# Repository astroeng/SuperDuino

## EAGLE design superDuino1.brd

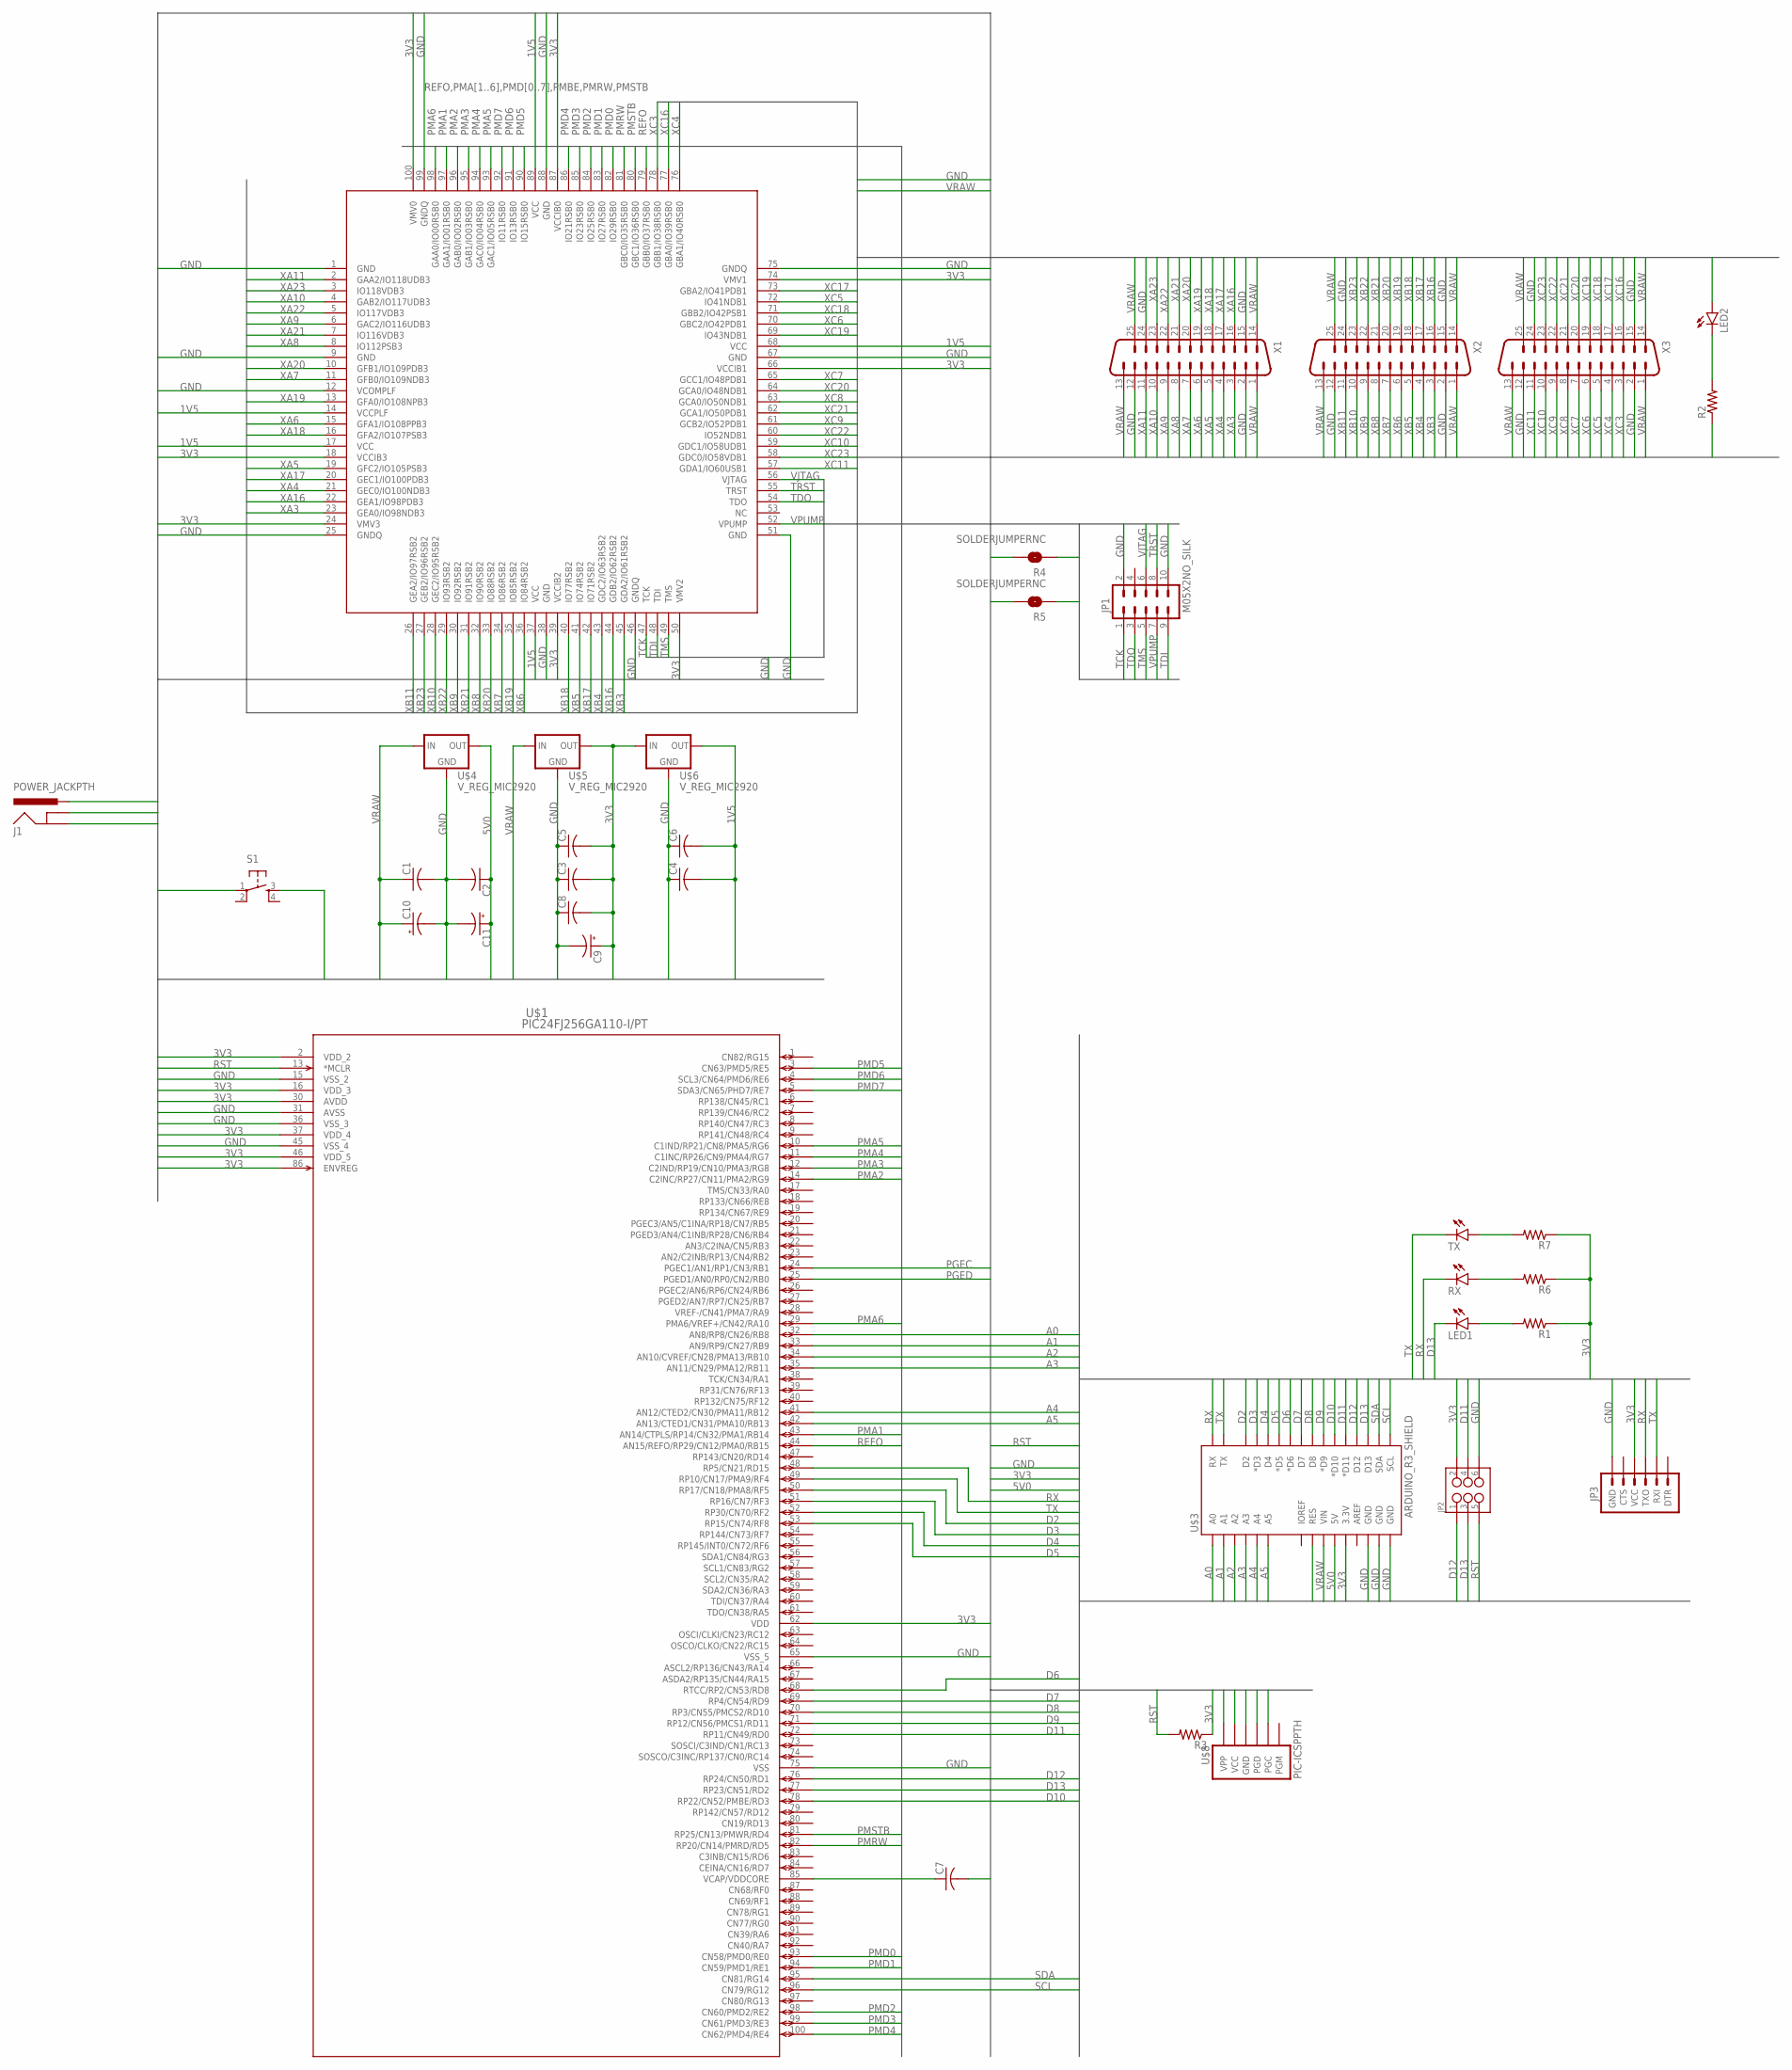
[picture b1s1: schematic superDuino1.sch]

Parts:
C1, C2, C3, C4, C5, C6, C8: C-USC0805; C0805
C7: C-US050-035X075; C050-035X075
C9, C10, C11: CPOL-USE2.5-6; E2,5-6
J1: POWER_JACKPTH; POWER_JACK_PTH
JP1: M05X2NO_SILK; 2X5_NOSILK
JP2: M03X22X3_SILK_SM; 2X3
JP3: ARDUINO_SERIAL_PROGRAMPTH; 1X06
LED1, LED2: LED1206; LED-1206
R1, R2, R3, R6, R7: R-US_R0805; R0805
R4, R5: SOLDERJUMPERNC; SJ_2S
RX: LED1206; LED-1206
S1: TAC_SWITCHPTH; TACTILE-PTH
TX: LED1206; LED-1206
U$1: PIC24FJ256GA110-I/PT; TQFP100_12X12MC
U$2: A3P250-VQ100; VQ100
U$3: ARDUINO_R3_SHIELD; UNO_R3_SHIELD
U$4, U$5, U$6: V_REG_MIC2920; SOT223
U$8: PIC-ICSPPTH; MOLEX-1X6
X1, X2, X3: DB25H; M25H

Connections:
1V5: C4.2, C6.2, U$2.14 (VCCPLF), U$2.17 (VCC), U$2.37 (VCC), U$2.68 (VCC), U$2.89 (VCC), U$6.3 (OUT)
3V3: C3.2, C5.2, C8.2, C9.+, JP2.2, JP3.VCC, R1.1, R3.1, R4.2, R5.2, R6.1, R7.1, U$1.2 (VDD_2), U$1.16 (VDD_3), U$1.30 (AVDD), U$1.37 (VDD_4), U$1.46 (VDD_5), U$1.62 (VDD), U$1.86 (ENVREG), U$2.18 (VCCIB3), U$2.24 (VMV3), U$2.39 (VCCIB2), U$2.50 (VMV2), U$2.66 (VCCIB1), U$2.74 (VMV1), U$2.87 (VCCIB0), U$2.100 (VMV0), U$3.3.3V, U$5.3 (OUT), U$6.1 (IN), U$8.5 (VCC)
5V0: C2.1, C11.+, U$3.5V, U$4.3 (OUT)
A0: U$1.32 (AN8/RP8/CN26/RB8), U$3.A0
A1: U$1.33 (AN9/RP9/CN27/RB9), U$3.A1
A2: U$1.34 (AN10/CVREF/CN28/PMA13/RB10), U$3.A2
A3: U$1.35 (AN11/CN29/PMA12/RB11), U$3.A3
A4: U$1.41 (AN12/CTED2/CN30/PMA11/RB12), U$3.A4
A5: U$1.42 (AN13/CTED1/CN31/PMA10/RB13), U$3.A5
D2: U$1.50 (RP17/CN18/PMA8/RF5), U$3.D2
D3: U$1.51 (RP16/CN7/RF3), U$3.D3 (*D3)
D4: U$1.52 (RP30/CN70/RF2), U$3.D4
D5: U$1.53 (RP15/CN74/RF8), U$3.D5 (*D5)
D6: U$1.68 (RTCC/RP2/CN53/RD8), U$3.D6 (*D6)
D7: U$1.69 (RP4/CN54/RD9), U$3.D7
D8: U$1.70 (RP3/CN55/PMCS2/RD10), U$3.D8
D9: U$1.71 (RP12/CN56/PMCS1/RD11), U$3.D9 (*D9)
D10: U$1.78 (RP22/CN52/PMBE/RD3), U$3.D10 (*D10)
D11: JP2.4, U$1.72 (RP11/CN49/RD0), U$3.D11 (*D11)
D12: JP2.1, U$1.76 (RP24/CN50/RD1), U$3.D12
D13: JP2.3, LED1.C, U$1.77 (RP23/CN51/RD2), U$3.D13
GND: C1.2, C2.2, C3.1, C4.1, C5.1, C6.1, C7.2, C8.1, C9.-, C10.-, C11.-, J1.GND, J1.GNDBREAK, JP1.2, JP1.10, JP2.6, JP3.GND, R2.1, S1.1, U$1.15 (VSS_2), U$1.31 (AVSS), U$1.36 (VSS_3), U$1.45 (VSS_4), U$1.65 (VSS_5), U$1.75 (VSS), U$2.1 (GND), U$2.9 (GND), U$2.12 (VCOMPLF), U$2.25 (GNDQ), U$2.38 (GND), U$2.46 (GNDQ), U$2.51 (GND), U$2.67 (GND), U$2.75 (GNDQ), U$2.88 (GND), U$2.99 (GNDQ), U$3.GND@0 (GND), U$3.GND@1 (GND), U$3.GND@2 (GND), U$4.2 (GND), U$5.2 (GND), U$6.2 (GND), U$8.4 (GND), X1.2, X1.12, X1.15, X1.24, X2.2, X2.12, X2.15, X2.24, X3.2, X3.12, X3.15, X3.24
unnamed: LED1.A, R1.2
unnamed: C7.1, U$1.85 (VCAP/VDDCORE)
unnamed: LED2.C, R2.2
unnamed: R7.2, TX.A
unnamed: R6.2, RX.A
PGEC: U$1.24 (PGEC1/AN1/RP1/CN3/RB1), U$8.2 (PGC)
PGED: U$1.25 (PGED1/AN0/RP0/CN2/RB0), U$8.3 (PGD)
PMA1: U$1.43 (AN14/CTPLS/RP14/CN32/PMA1/RB14), U$2.97 (GAA1/IO01RSB0)
PMA2: U$1.14 (C2INC/RP27/CN11/PMA2/RG9), U$2.96 (GAB0/IO02RSB0)
PMA3: U$1.12 (C2IND/RP19/CN10/PMA3/RG8), U$2.95 (GAB1/IO03RSB0)
PMA4: U$1.11 (C1INC/RP26/CN9/PMA4/RG7), U$2.94 (GAC0/IO04RSB0)
PMA5: U$1.10 (C1IND/RP21/CN8/PMA5/RG6), U$2.93 (GAC1/IO05RSB0)
PMA6: U$1.29 (PMA6/VREF+/CN42/RA10), U$2.98 (GAA0/IO00RSB0)
PMD0: U$1.93 (CN58/PMD0/RE0), U$2.82 (IO29RSB0)
PMD1: U$1.94 (CN59/PMD1/RE1), U$2.83 (IO27RSB0)
PMD2: U$1.98 (CN60/PMD2/RE2), U$2.84 (IO25RSB0)
PMD3: U$1.99 (CN61/PMD3/RE3), U$2.85 (IO23RSB0)
PMD4: U$1.100 (CN62/PMD4/RE4), U$2.86 (IO21RSB0)
PMD5: U$1.3 (CN63/PMD5/RE5), U$2.90 (IO15RSB0)
PMD6: U$1.4 (SCL3/CN64/PMD6/RE6), U$2.91 (IO13RSB0)
PMD7: U$1.5 (SDA3/CN65/PHD7/RE7), U$2.92 (IO11RSB0)
PMRW: U$1.82 (RP20/CN14/PMRD/RD5), U$2.81 (GBC0/IO35RSB0)
PMSTB: U$1.81 (RP25/CN13/PMWR/RD4), U$2.80 (GBC1/IO36RSB0)
REFO: U$1.44 (AN15/REFO/RP29/CN12/PMA0/RB15), U$2.79 (GBB0/IO37RSB0)
RST: JP2.5, R3.2, S1.3, U$1.13 (*MCLR), U$3.RES, U$8.6 (VPP)
RX: JP3.TXO, RX.C, U$1.48 (RP5/CN21/RD15), U$3.RX
SCL: U$1.96 (CN79/RG12), U$3.SCL
SDA: U$1.95 (CN81/RG14), U$3.SDA
TCK: JP1.1, U$2.47 (TCK)
TDI: JP1.9, U$2.48 (TDI)
TDO: JP1.3, U$2.54 (TDO)
TMS: JP1.5, U$2.49 (TMS)
TRST: JP1.8, U$2.55 (TRST)
TX: JP3.RXI, TX.C, U$1.49 (RP10/CN17/PMA9/RF4), U$3.TX
VJTAG: JP1.6, R5.1, U$2.56 (VJTAG)
VPUMP: JP1.7, R4.1, U$2.52 (VPUMP)
VRAW: C1.1, C10.+, J1.PWR, U$3.VIN, U$4.1 (IN), U$5.1 (IN), X1.1, X1.13, X1.14, X1.25, X2.1, X2.13, X2.14, X2.25, X3.1, X3.13, X3.14, X3.25
XA3: U$2.23 (GEA0/IO98NDB3), X1.3
XA4: U$2.21 (GEC0/IO100NDB3), X1.4
XA5: U$2.19 (GFC2/IO105PSB3), X1.5
XA6: U$2.15 (GFA1/IO108PPB3), X1.6
XA7: U$2.11 (GFB0/IO109NDB3), X1.7
XA8: U$2.8 (IO112PSB3), X1.8
XA9: U$2.6 (GAC2/IO116UDB3), X1.9
XA10: U$2.4 (GAB2/IO117UDB3), X1.10
XA11: U$2.2 (GAA2/IO118UDB3), X1.11
XA16: U$2.22 (GEA1/IO98PDB3), X1.16
XA17: U$2.20 (GEC1/IO100PDB3), X1.17
XA18: U$2.16 (GFA2/IO107PSB3), X1.18
XA19: U$2.13 (GFA0/IO108NPB3), X1.19
XA20: U$2.10 (GFB1/IO109PDB3), X1.20
XA21: U$2.7 (IO116VDB3), X1.21
XA22: U$2.5 (IO117VDB3), X1.22
XA23: U$2.3 (IO118VDB3), X1.23
XB3: U$2.45 (GDA2/IO61RSB2), X2.3
XB4: U$2.43 (GDC2/IO63RSB2), X2.4
XB5: U$2.41 (IO74RSB2), X2.5
XB6: U$2.36 (IO84RSB2), X2.6
XB7: U$2.34 (IO86RSB2), X2.7
XB8: U$2.32 (IO90RSB2), X2.8
XB9: U$2.30 (IO92RSB2), X2.9
XB10: U$2.28 (GEC2/IO95RSB2), X2.10
XB11: U$2.26 (GEA2/IO97RSB2), X2.11
XB16: U$2.44 (GDB2/IO62RSB2), X2.16
XB17: U$2.42 (IO71RSB2), X2.17
XB18: U$2.40 (IO77RSB2), X2.18
XB19: U$2.35 (IO85RSB2), X2.19
XB20: U$2.33 (IO88RSB2), X2.20
XB21: LED2.A, U$2.31 (IO91RSB2), X2.21
XB22: U$2.29 (IO93RSB2), X2.22
XB23: U$2.27 (GEB2/IO96RSB2), X2.23
XC3: U$2.78 (GBB1/IO38RSB0), X3.3
XC4: U$2.76 (GBA1/IO40RSB0), X3.4
XC5: U$2.72 (IO41NDB1), X3.5
XC6: U$2.70 (GBC2/IO42PDB1), X3.6
XC7: U$2.65 (GCC1/IO48PDB1), X3.7
XC8: U$2.63 (GCA0/IO50NDB1), X3.8
XC9: U$2.61 (GCB2/IO52PDB1), X3.9
XC10: U$2.59 (GDC1/IO58UDB1), X3.10
XC11: U$2.57 (GDA1/IO60USB1), X3.11
XC16: U$2.77 (GBA0/IO39RSB0), X3.16
XC17: U$2.73 (GBA2/IO41PDB1), X3.17
XC18: U$2.71 (GBB2/IO42PSB1), X3.18
XC19: U$2.69 (IO43NDB1), X3.19
XC20: U$2.64 (GCA0/IO48NDB1), X3.20
XC21: U$2.62 (GCA1/IO50PDB1), X3.21
XC22: U$2.60 (IO52NDB1), X3.22
XC23: U$2.58 (GDC0/IO58VDB1), X3.23

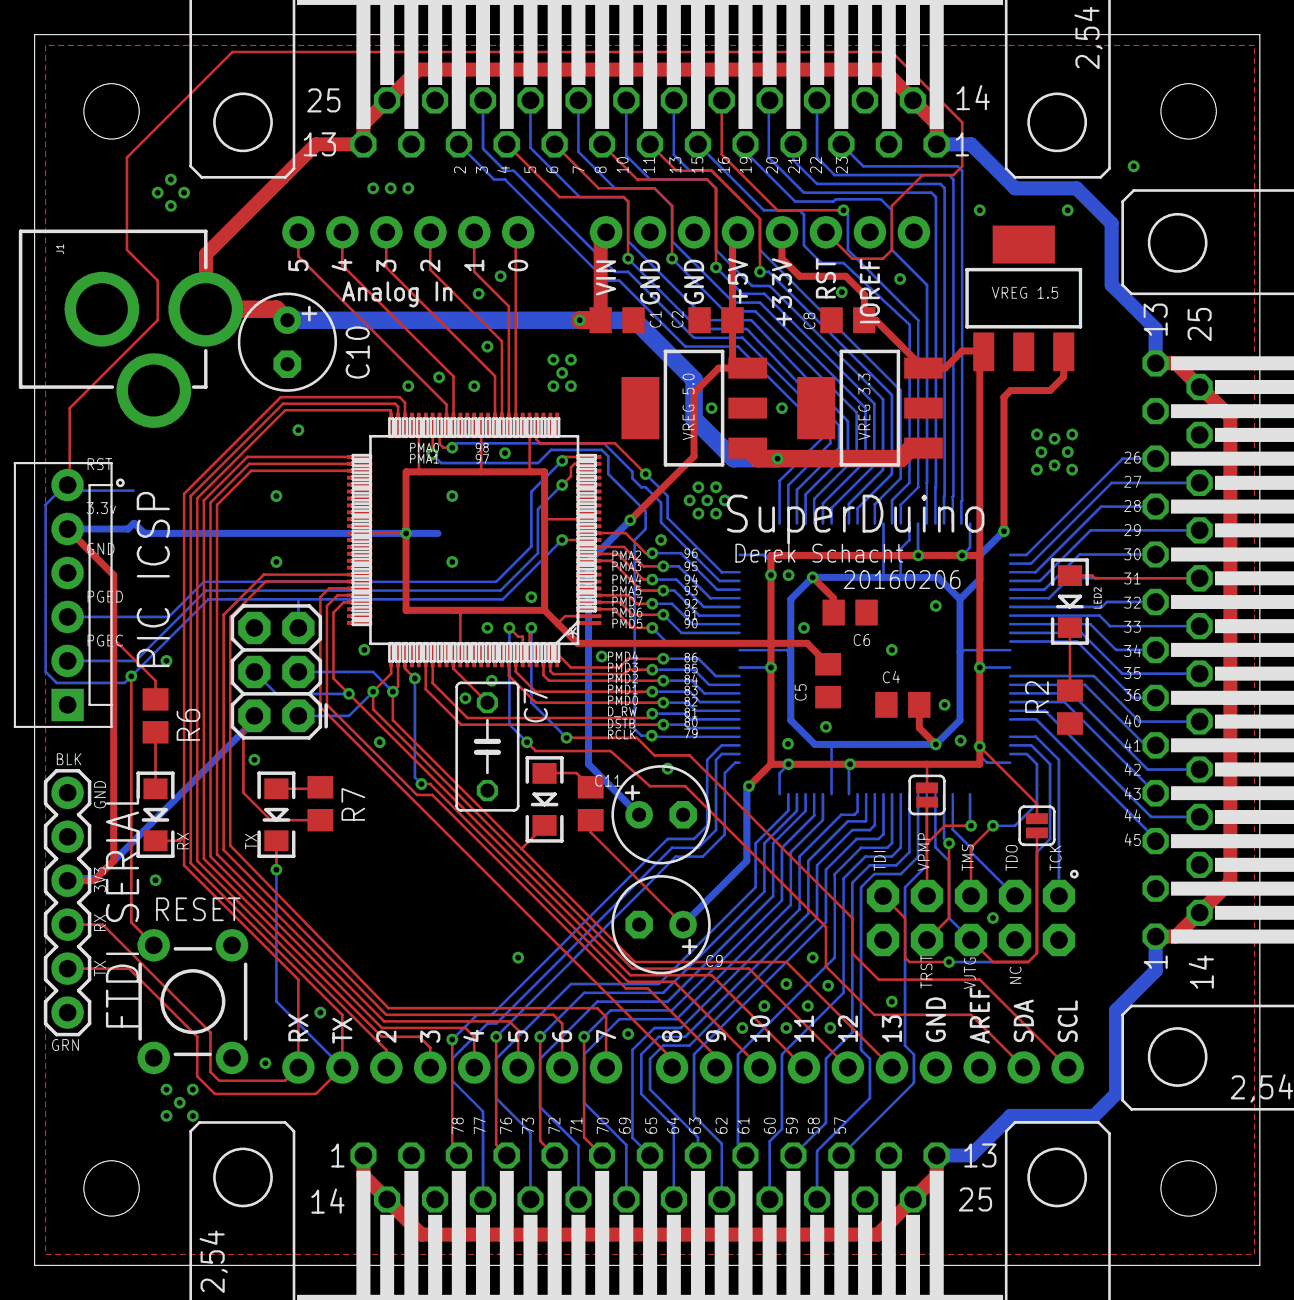
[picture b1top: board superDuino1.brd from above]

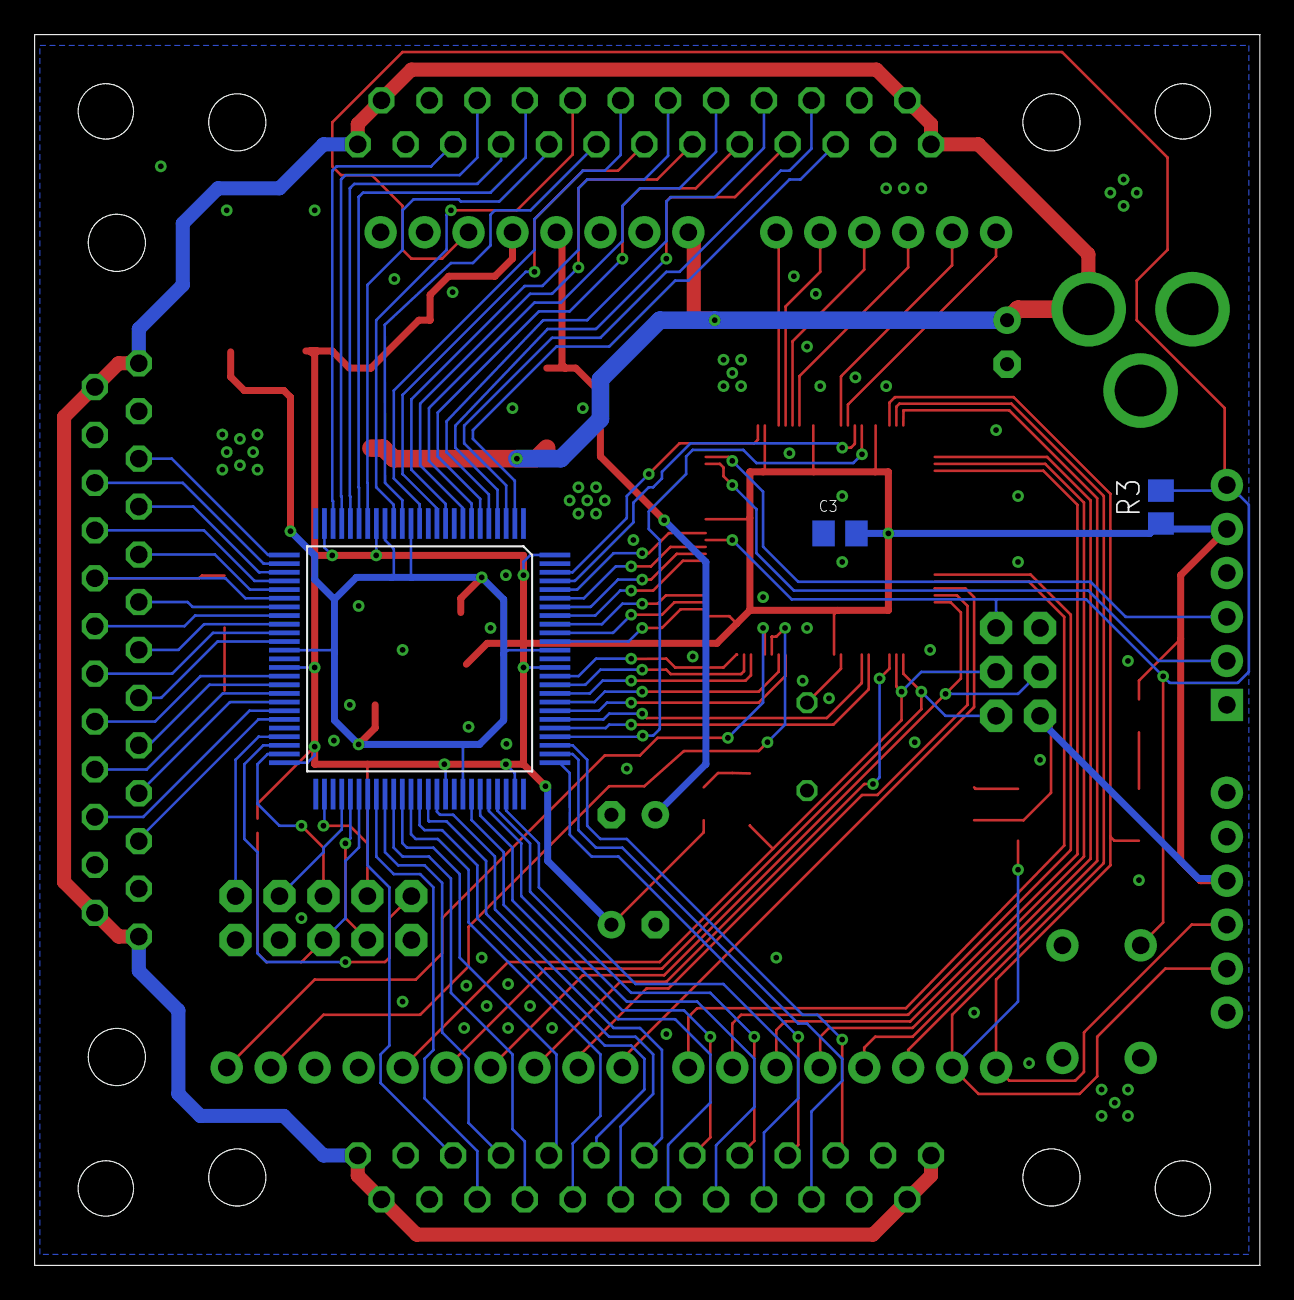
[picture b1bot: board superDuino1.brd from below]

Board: 2 copper layers, 70.8 x 71.1 mm, 37 parts (3 on the bottom side), 110 nets.

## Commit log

2016-01-17 SuperDuino initial commit.
2016-02-08 Added a BOM file and updated schematic and layout to address: Issue #7, Issue #6, Issue #5, Issue #4, Issue #3, Issue #2, Issue #1

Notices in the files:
parts and their libraries:
SparkFun-Connectors: Licensing: Creative Commons ShareAlike 4.0 International - https://creativecommons.org/licenses/by-sa/4.0
COPYRIGHT: Copyright (C) 2015 Accelerated Designs. All rights reserved
